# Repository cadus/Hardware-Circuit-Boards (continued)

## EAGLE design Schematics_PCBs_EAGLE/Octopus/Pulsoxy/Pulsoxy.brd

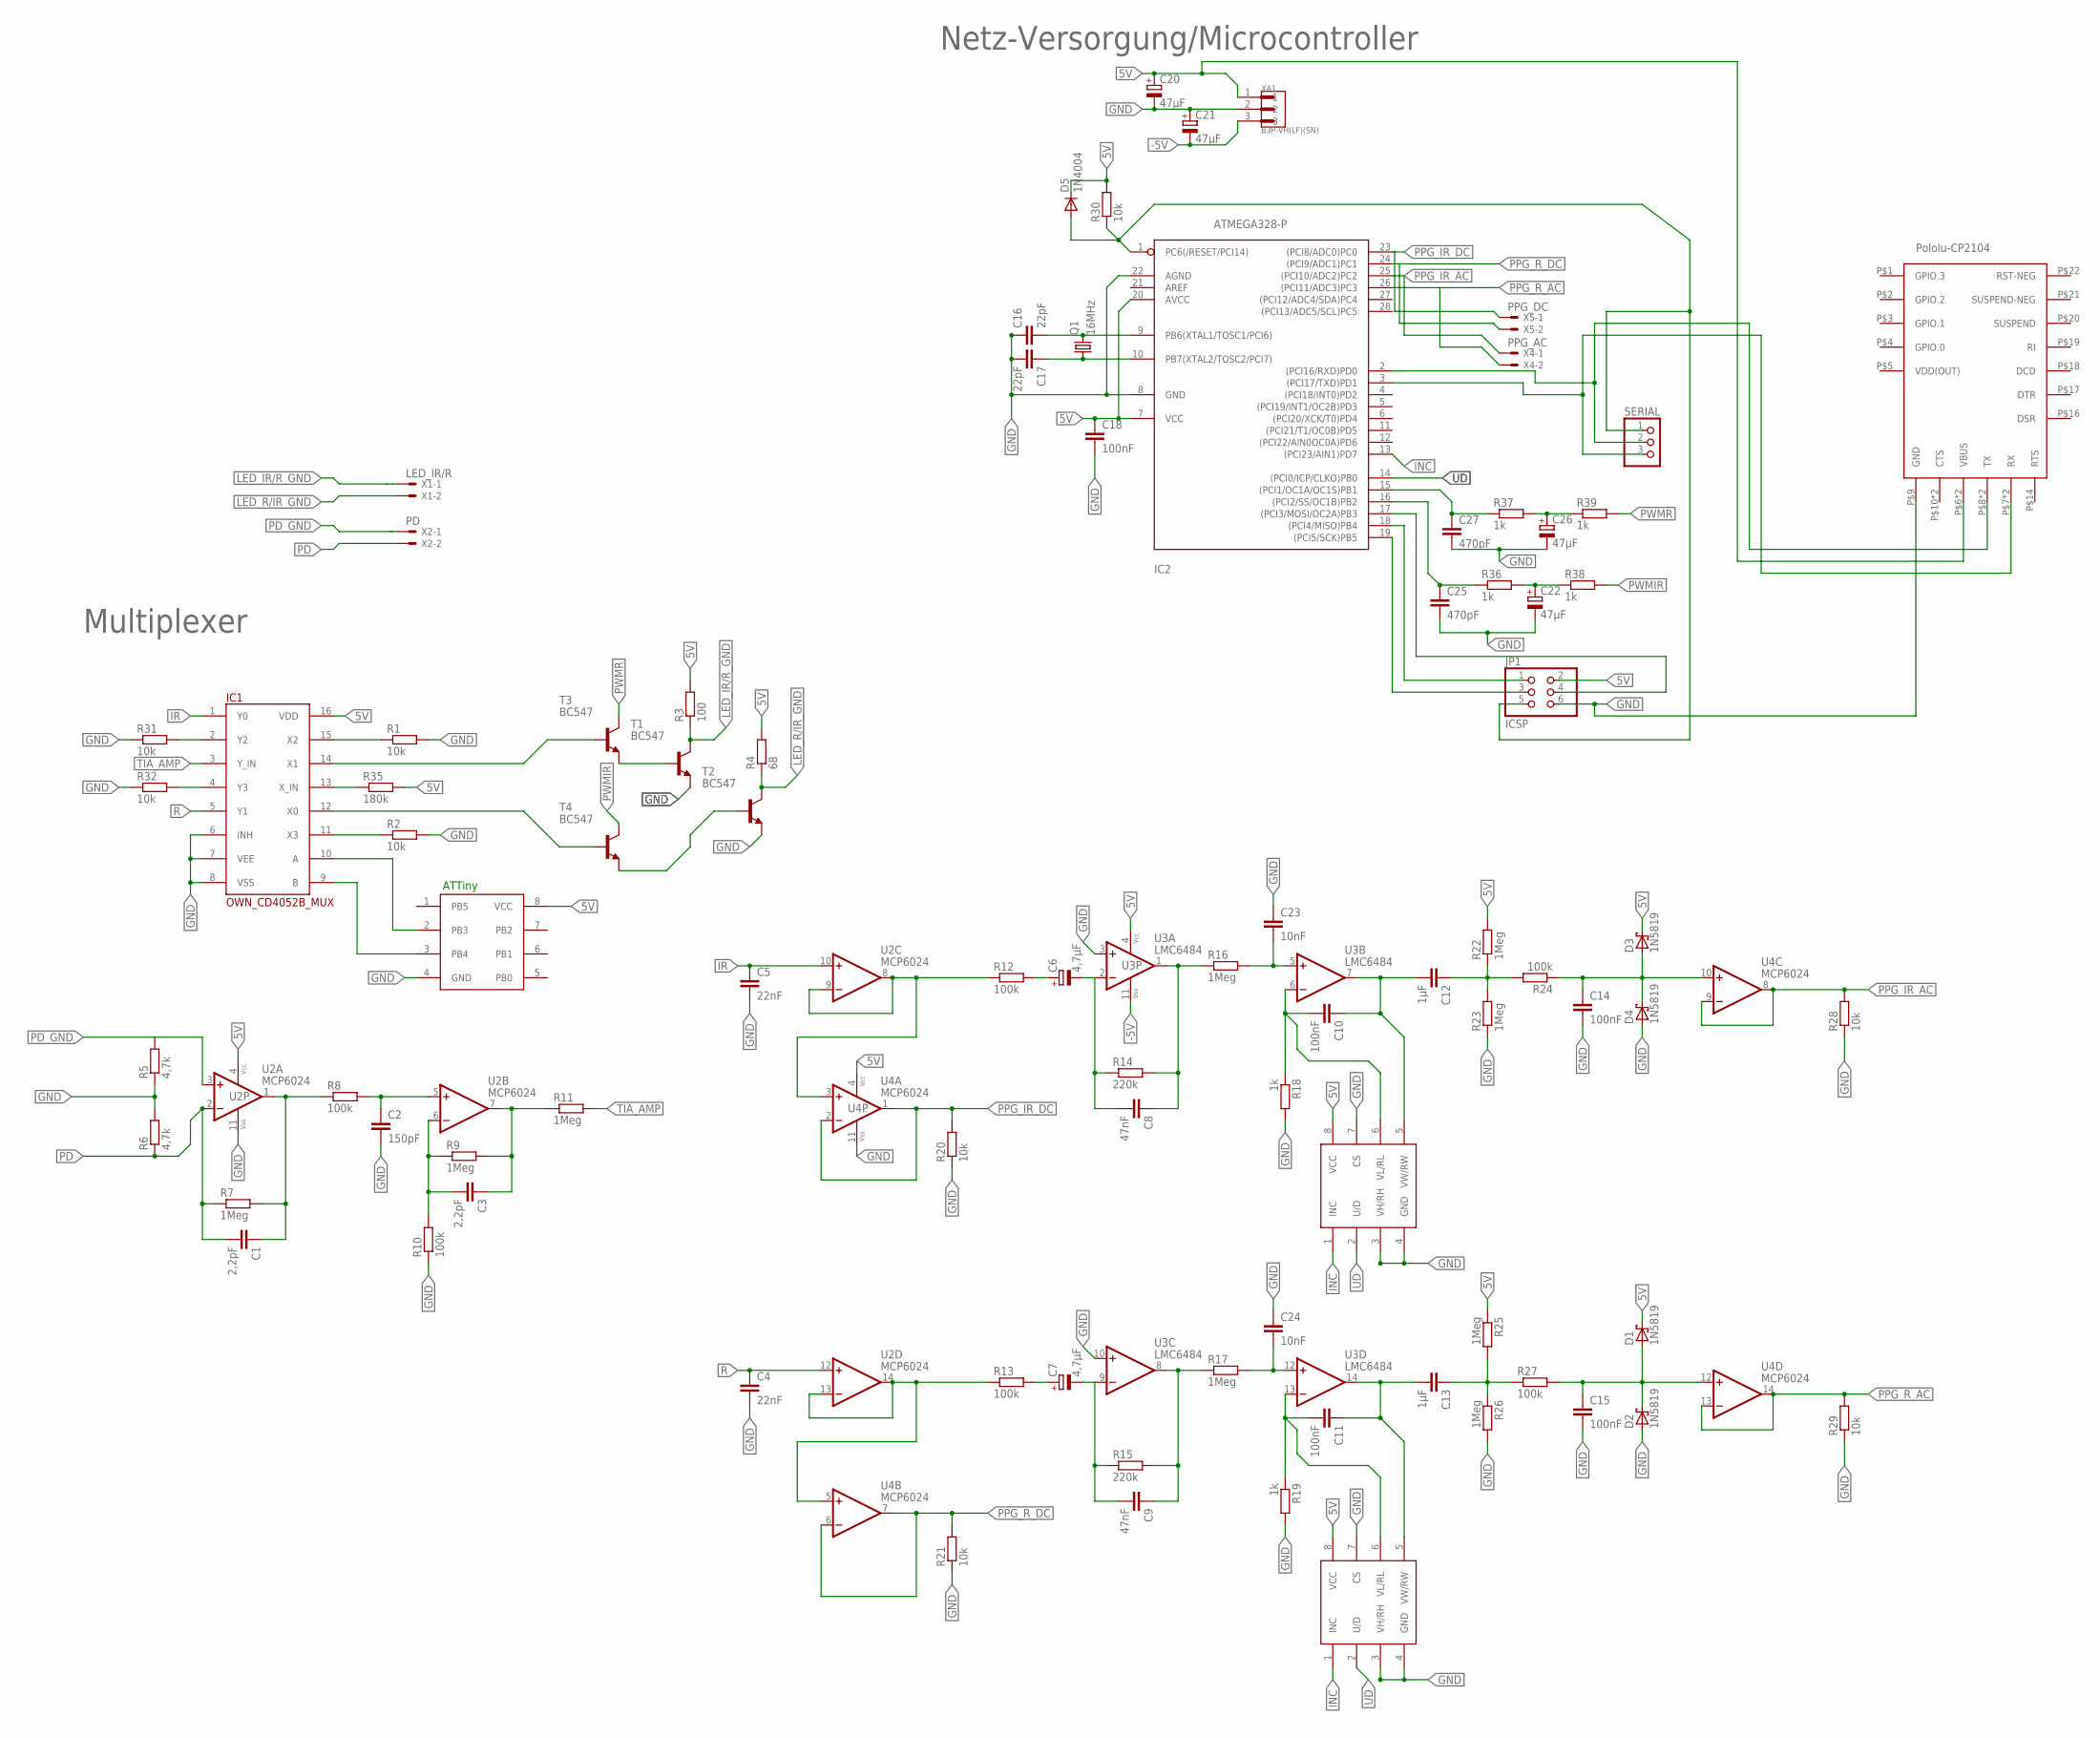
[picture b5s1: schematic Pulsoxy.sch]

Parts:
ATTINY: ATTINY85; DIL08
C1, C3: 2,2pF; C025-024X044
C2: 150pF; C025-024X044
C4, C5: 22nF; C025-024X044
C6, C7: 4,7µF; E2-5
C8, C9: 47nF; C025-024X044
C10, C11, C14, C15, C18: 100nF; C025-024X044
C12, C13: 1µF; C150-064X183
C16, C17: 22pF; C025-024X044
C20, C21, C22, C26: 47µF; E2,5-6E
C23, C24: 10nF; C025-024X044
C25, C27: 470pF; C025-024X044
D1, D2, D3, D4: 1N5819; F126Z12
D5: 1N4004; DO41-10
IC1: OWN_CD4052B_MUX; DIL16
IC2: ATMEGA328-P; DIL28-3
JP1: ICSP; 2X03
Q1: 16MHz; HC49U70
R1, R2, R20, R21, R28, R29, R30, R31, R32: 10k; 0204/7
R3: 100; 0204/7
R4: 68; 0204/7
R5, R6: 4,7k; 0204/7
R7, R9, R11, R16, R17, R22, R23, R25, R26: 1Meg; 0204/7
R8, R10, R12, R13, R24, R27: 100k; 0204/7
R14, R15: 220k; 0204/7
R18, R19, R36, R37, R38, R39: 1k; 0204/7
R35: 180k; 0204/7
SERIAL: PINHD-1X3; 1X03
T1, T2, T3, T4: BC547; TO92
U2, U4: MCP6024; DIL14
U3: LMC6484; DIL14
U$1, U$2: X9C104P; DIL08
U$3: POLOLU_CP2104; POLOLUCP2104
X1: LED_IR/R; JST-XH-02-PACKAGE-LONG-PAD
X2: PD; JST-XH-02-PACKAGE-LONG-PAD
X4: PPG_AC; JST-XH-02-PACKAGE-LONG-PAD
X5: PPG_DC; JST-XH-02-PACKAGE-LONG-PAD
XA1: B3P-VH(LF)(SN); JST_B3P-VH(LF)(SN)

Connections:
5V: ATTINY.8 (VCC), C18.1, C20.+, D1.C, D3.C, D5.C, IC1.16 (VDD), IC2.7 (VCC), IC2.20 (AVCC), JP1.2, R3.2, R4.2, R22.2, R25.1, R30.2, R35.2, U2.4 (VCC+), U3.4 (VCC+), U4.4 (VCC+), U$1.8 (VCC), U$2.8 (VCC), U$3.P$6 (VBUS), U$3.P$11 (VBUS), XA1.1
-5V: C21.-, U3.11 (VCC-), XA1.3
GND: ATTINY.4 (GND), C2.2, C4.2, C5.2, C14.2, C15.2, C16.1, C17.2, C18.2, C20.-, C21.+, C22.-, C23.1, C24.1, C25.2, C26.-, C27.2, D2.A, D4.A, IC1.6 (INH), IC1.7 (VEE), IC1.8 (VSS), IC2.8 (GND), IC2.22 (AGND), JP1.6, R1.2, R2.2, R5.1, R6.2, R10.1, R18.2, R19.2, R20.1, R21.1, R23.1, R26.2, R28.1, R29.1, R31.1, R32.1, T1.1 (E), T2.1 (E), U2.11 (VCC-), U3.3 (+IN), U3.10 (+IN), U4.11 (VCC-), U$1.3 (VH/RH), U$1.4 (GND), U$1.7 (CS), U$2.3 (VH/RH), U$2.4 (GND), U$2.7 (CS), U$3.P$9 (GND), XA1.2
INC: IC2.13 ((PCI23/AIN1)PD7), U$1.1 (INC), U$2.1 (INC)
IR: C5.1, IC1.1 (Y0), U2.10 (+IN)
LED_IR/R_GND: R3.1, T1.3 (C), X1.1
LED_R/IR_GND: R4.1, T2.3 (C), X1.2
unnamed: IC1.11 (X3), R2.1
unnamed: IC1.15 (X2), R1.1
unnamed: IC1.14 (X1), T3.2 (B)
unnamed: IC1.12 (X0), T4.2 (B)
unnamed: C1.1, R7.2, R8.1, U2.1 (OUT)
unnamed: C2.1, R8.2, U2.5 (+IN)
unnamed: C3.2, R9.1, R10.2, U2.6 (-IN)
unnamed: C3.1, R9.2, R11.1, U2.7 (OUT)
unnamed: R12.1, U2.8 (OUT), U2.9 (-IN), U4.3 (+IN)
unnamed: R13.1, U2.13 (-IN), U2.14 (OUT), U4.5 (+IN)
unnamed: ATTINY.2 (PB3), IC1.10 (A)
unnamed: ATTINY.3 (PB4), IC1.9 (B)
unnamed: C7.-, C9.2, R15.1, U3.9 (-IN)
unnamed: C8.1, R14.2, R16.1, U3.1 (OUT)
unnamed: C6.-, C8.2, R14.1, U3.2 (-IN)
unnamed: C9.1, R15.2, R17.1, U3.8 (OUT)
unnamed: C13.1, R25.2, R26.1, R27.1
unnamed: C14.1, D3.A, D4.C, R24.1, U4.10 (+IN)
unnamed: C10.2, R18.1, U3.6 (-IN), U$1.6 (VL/RL)
unnamed: C15.1, D1.A, D2.C, R27.2, U4.12 (+IN)
unnamed: C11.2, R19.1, U3.13 (-IN), U$2.6 (VL/RL)
unnamed: IC1.4 (Y3), R32.2
unnamed: C10.1, C12.2, U3.7 (OUT), U$1.5 (VW/RW)
unnamed: C12.1, R22.1, R23.2, R24.2
unnamed: C11.1, C13.2, U3.14 (OUT), U$2.5 (VW/RW)
unnamed: C16.2, IC2.9 (PB6(XTAL1/TOSC1/PCI6)), Q1.2
unnamed: C17.1, IC2.10 (PB7(XTAL2/TOSC2/PCI7)), Q1.1
unnamed: IC2.2 ((PCI16/RXD)PD0), SERIAL.2, U$3.P$8 (TX), U$3.P$12 (TX)
unnamed: D5.A, IC2.1 (PC6(/RESET/PCI14)), JP1.5, R30.1, SERIAL.1
unnamed: IC2.18 ((PCI4/MISO)PB4), JP1.1
unnamed: IC2.19 ((PCI5/SCK)PB5), JP1.3
unnamed: IC2.17 ((PCI3/MOSI/OC2A)PB3), JP1.4
unnamed: IC1.2 (Y2), R31.2
unnamed: IC2.3 ((PCI17/TXD)PD1), SERIAL.3, U$3.P$7 (RX), U$3.P$13 (RX)
unnamed: C24.2, R17.2, U3.12 (+IN)
unnamed: IC1.13 (X_IN), R35.1
unnamed: C25.1, IC2.16 ((PCI2/SS/OC1B)PB2), R36.1
unnamed: C23.2, R16.2, U3.5 (+IN)
unnamed: C7.+, R13.2
unnamed: C6.+, R12.2
unnamed: T1.2 (B), T3.1 (E)
unnamed: T2.2 (B), T4.1 (E)
unnamed: C22.+, R36.2, R38.1
unnamed: C27.1, IC2.15 ((PCI1/OC1A/OC1S)PB1), R37.1
unnamed: C26.+, R37.2, R39.1
PD: C1.2, R6.1, R7.1, U2.2 (-IN), X2.2
PD_GND: R5.2, U2.3 (+IN), X2.1
PPG_IR_AC: IC2.25 ((PCI10/ADC2)PC2), R28.2, U4.8 (OUT), U4.9 (-IN), X4.1
PPG_IR_DC: IC2.23 ((PCI8/ADC0)PC0), R20.2, U4.1 (OUT), U4.2 (-IN), X5.1
PPG_R_AC: IC2.26 ((PCI11/ADC3)PC3), R29.2, U4.13 (-IN), U4.14 (OUT), X4.2
PPG_R_DC: IC2.24 ((PCI9/ADC1)PC1), R21.2, U4.6 (-IN), U4.7 (OUT), X5.2
PWMIR: R38.2, T4.3 (C)
PWMR: R39.2, T3.3 (C)
R: C4.1, IC1.5 (Y1), U2.12 (+IN)
TIA_AMP: IC1.3 (Y_IN), R11.2
UD: IC2.14 ((PCI0/ICP/CLKO)PB0), U$1.2 (U/D), U$2.2 (U/D)
VDD(OUT): U$3.P$5 (VDD(OUT))

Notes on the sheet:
ATTiny
Netz-Versorgung/Microcontroller
Multiplexer

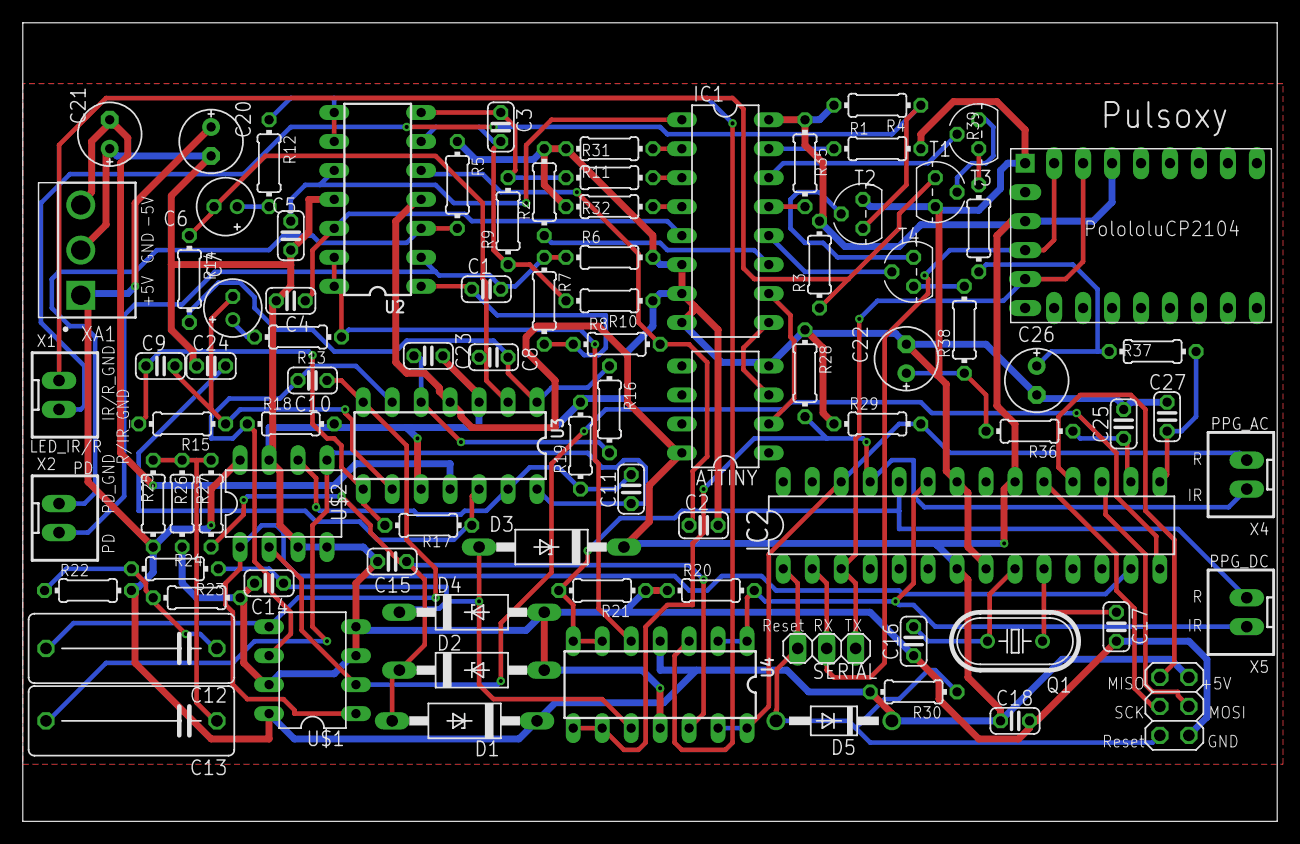
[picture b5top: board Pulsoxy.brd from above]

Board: 2 copper layers, 110.0 x 70.0 mm, 89 parts (0 on the bottom side), 63 nets.

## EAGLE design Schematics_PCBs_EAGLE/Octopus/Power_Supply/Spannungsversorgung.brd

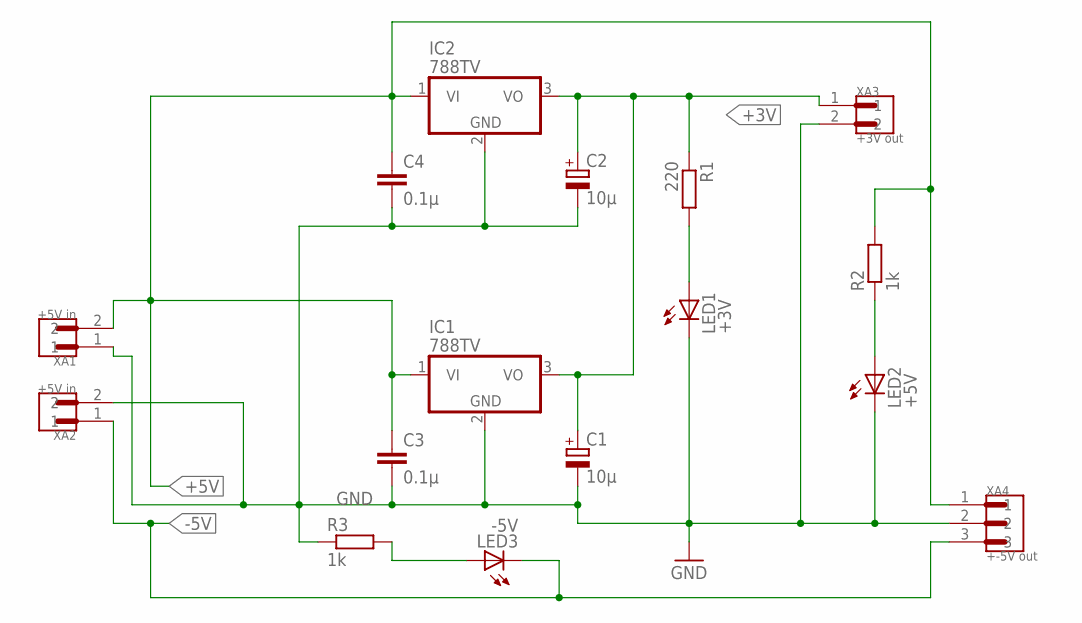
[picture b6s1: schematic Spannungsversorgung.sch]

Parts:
C1, C2: 10µ; E2,5-6
C3, C4: 0.1µ; C2.5-3
IC1, IC2: 788TV; TO220V
LED1: +3V; LED3MM
LED2: +5V; LED3MM
LED3: -5V; LED3MM
R1: 220; 0207/7
R2, R3: 1k; 0207/7
XA1, XA2: +5V in; JST_B2P-VH(LF)(SN)
XA3: +3V out; JST_B2P-VH(LF)(SN)
XA4: +-5V out; JST_B3P-VH(LF)(SN)

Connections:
+3V: C1.+, C2.+, IC1.3 (VO), IC2.3 (VO), R1.1, XA3.1
+5V: C3.1, C4.1, IC1.1 (VI), IC2.1 (VI), R2.2, XA1.2, XA4.1
-5V: LED3.K (C), XA2.1, XA4.3
GND: C1.-, C2.-, C3.2, C4.2, IC1.2 (GND), IC2.2 (GND), LED1.K (C), LED2.K (C), R3.1, XA1.1, XA2.2, XA3.2, XA4.2
unnamed: LED3.A, R3.2
unnamed: LED1.A, R1.2
unnamed: LED2.A, R2.1

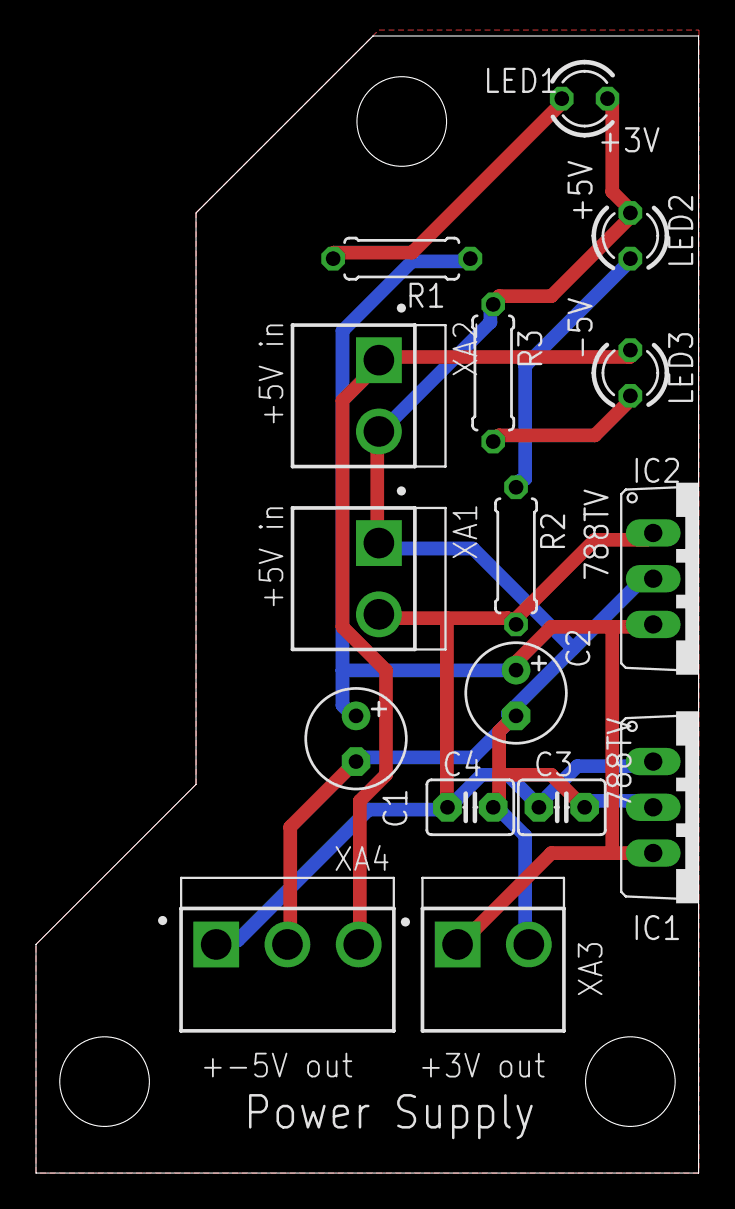
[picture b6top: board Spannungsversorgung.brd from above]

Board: 2 copper layers, 36.8 x 63.2 mm, 16 parts (0 on the bottom side), 7 nets.

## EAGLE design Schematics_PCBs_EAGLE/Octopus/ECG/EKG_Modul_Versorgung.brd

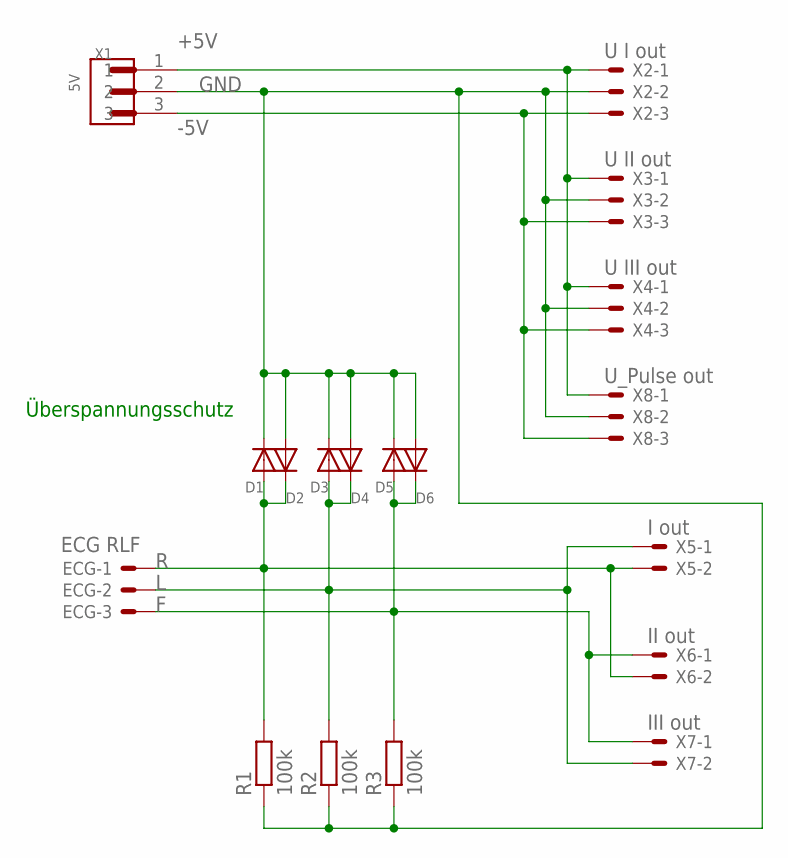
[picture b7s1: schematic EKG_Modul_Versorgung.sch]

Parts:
D1, D2, D3, D4, D5, D6: DIODEDO-1N4148; DO-1N4148
ECG: ECG RLF; JST-XH-03-PACKAGE-LONG-PAD
R1, R2, R3: 100k; 0207/7
X1: 5V; JST_B3P-VH(LF)(SN)
X2: U I out; JST-XH-03-PACKAGE-LONG-PAD
X3: U II out; JST-XH-03-PACKAGE-LONG-PAD
X4: U III out; JST-XH-03-PACKAGE-LONG-PAD
X5: I out; JST-XH-02-PACKAGE-LONG-PAD
X6: II out; JST-XH-02-PACKAGE-LONG-PAD
X7: III out; JST-XH-02-PACKAGE-LONG-PAD
X8: U_Pulse out; JST-XH-03-PACKAGE-LONG-PAD

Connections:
+5V: X1.1, X2.1, X3.1, X4.1, X8.1
-5V: X1.3, X2.3, X3.3, X4.3, X8.3
F: D5.A, D6.C, ECG.3, R3.2, X6.1, X7.1
GND: D1.C, D2.A, D3.C, D4.A, D5.C, D6.A, R1.1, R2.1, R3.1, X1.2, X2.2, X3.2, X4.2, X8.2
L: D3.A, D4.C, ECG.2, R2.2, X5.1, X7.2
R: D1.A, D2.C, ECG.1, R1.2, X5.2, X6.2

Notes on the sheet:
Überspannungsschutz

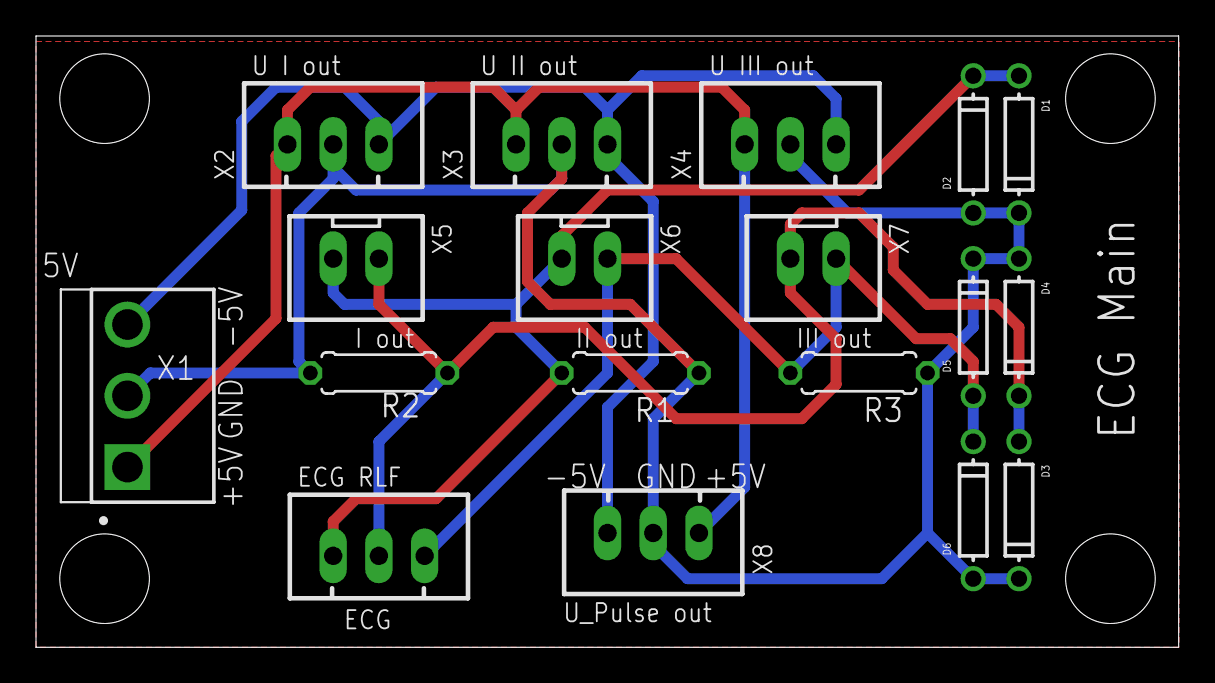
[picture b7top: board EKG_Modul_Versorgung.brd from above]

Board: 2 copper layers, 63.5 x 34.0 mm, 18 parts (0 on the bottom side), 6 nets.

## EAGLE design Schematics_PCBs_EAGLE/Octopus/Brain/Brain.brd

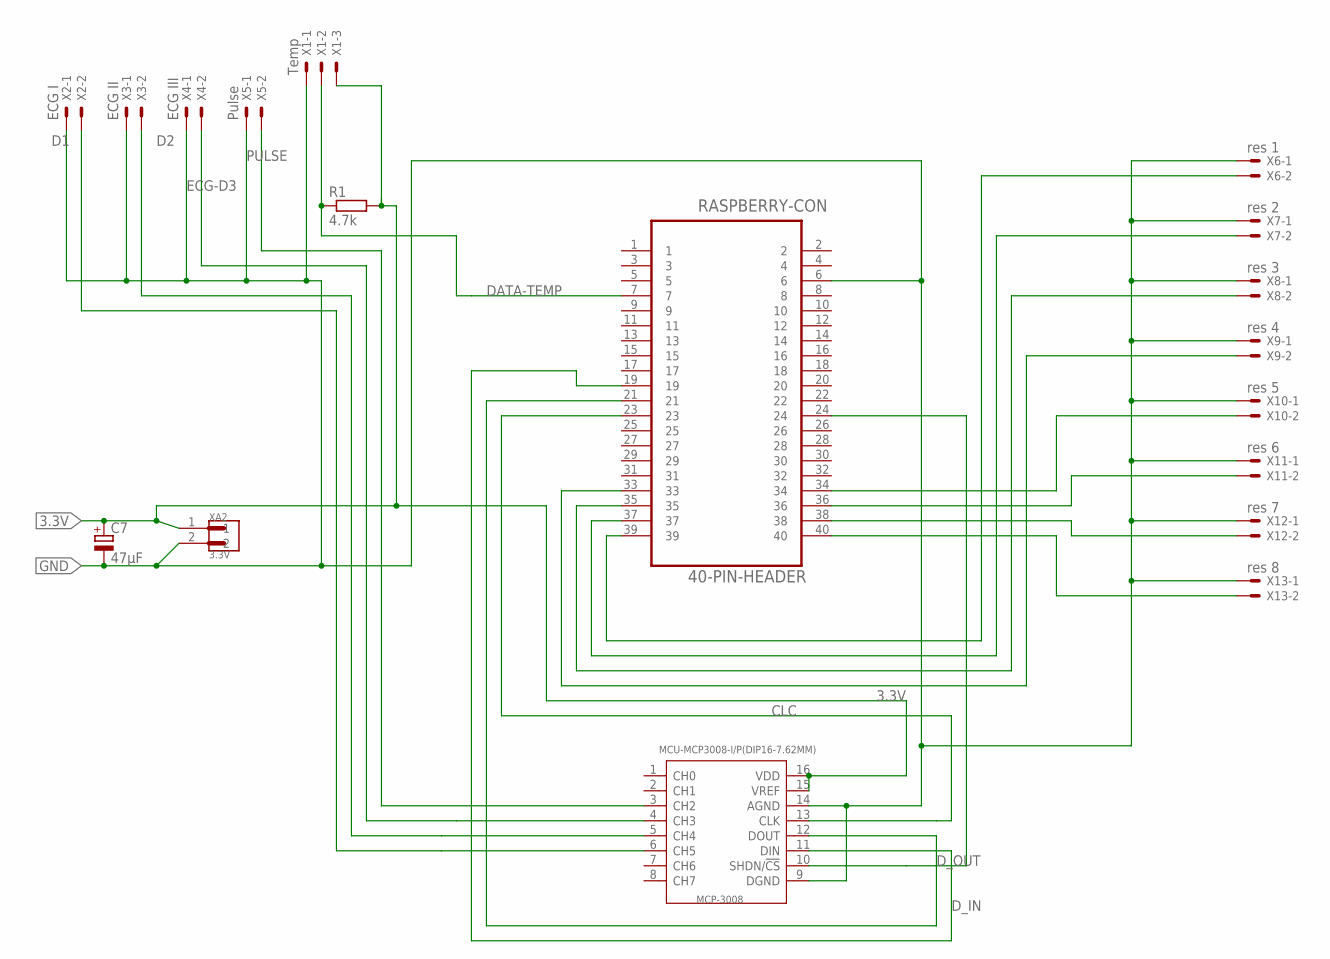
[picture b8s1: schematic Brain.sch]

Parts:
C7: 47µF; E2,5-6E
MCP-3008: MCU-MCP3008-I/P(DIP16-7.62MM); DIP16-2.54-19.2X7.62MM
R1: 4.7k; 0207/7
RASPBERRY-CON: 40-PIN-HEADER; SAMTEC_TSW-120-09-F-Q
X1: Temp; JST-XH-03-PACKAGE-LONG-PAD
X2: ECG I; JST-XH-02-PACKAGE-LONG-PAD
X3: ECG II; JST-XH-02-PACKAGE-LONG-PAD
X4: ECG III; JST-XH-02-PACKAGE-LONG-PAD
X5: Pulse; JST-XH-02-PACKAGE-LONG-PAD
X6: res 1; JST-XH-02-PACKAGE-LONG-PAD
X7: res 2; JST-XH-02-PACKAGE-LONG-PAD
X8: res 3; JST-XH-02-PACKAGE-LONG-PAD
X9: res 4; JST-XH-02-PACKAGE-LONG-PAD
X10: res 5; JST-XH-02-PACKAGE-LONG-PAD
X11: res 6; JST-XH-02-PACKAGE-LONG-PAD
X12: res 7; JST-XH-02-PACKAGE-LONG-PAD
X13: res 8; JST-XH-02-PACKAGE-LONG-PAD
XA2: 3.3V; JST_B2P-VH(LF)(SN)

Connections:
3.3V: C7.+, MCP-3008.15 (VREF), MCP-3008.16 (VDD), R1.2, X1.3, XA2.1
CLC: MCP-3008.13 (CLK), RASPBERRY-CON.23
D1: MCP-3008.6 (CH5), X2.2
D2: MCP-3008.5 (CH4), X3.2
DATA-TEMP: R1.1, RASPBERRY-CON.7, X1.2
D_IN: MCP-3008.11 (DIN), RASPBERRY-CON.19
D_OUT: MCP-3008.12 (DOUT), RASPBERRY-CON.21
ECG-D3: MCP-3008.4 (CH3), X4.2
GND: C7.-, MCP-3008.9 (DGND), MCP-3008.14 (AGND), RASPBERRY-CON.6, X1.1, X2.1, X3.1, X4.1, X5.1, X6.1, X7.1, X8.1, X9.1, X10.1, X11.1, X12.1, X13.1, XA2.2
unnamed: RASPBERRY-CON.40, X13.2
unnamed: RASPBERRY-CON.38, X12.2
unnamed: MCP-3008.10 (SHDN/!CS), RASPBERRY-CON.24
unnamed: RASPBERRY-CON.36, X11.2
unnamed: RASPBERRY-CON.34, X10.2
unnamed: RASPBERRY-CON.39, X6.2
unnamed: RASPBERRY-CON.37, X7.2
unnamed: RASPBERRY-CON.35, X8.2
unnamed: RASPBERRY-CON.33, X9.2
PULSE: MCP-3008.3 (CH2), X5.2

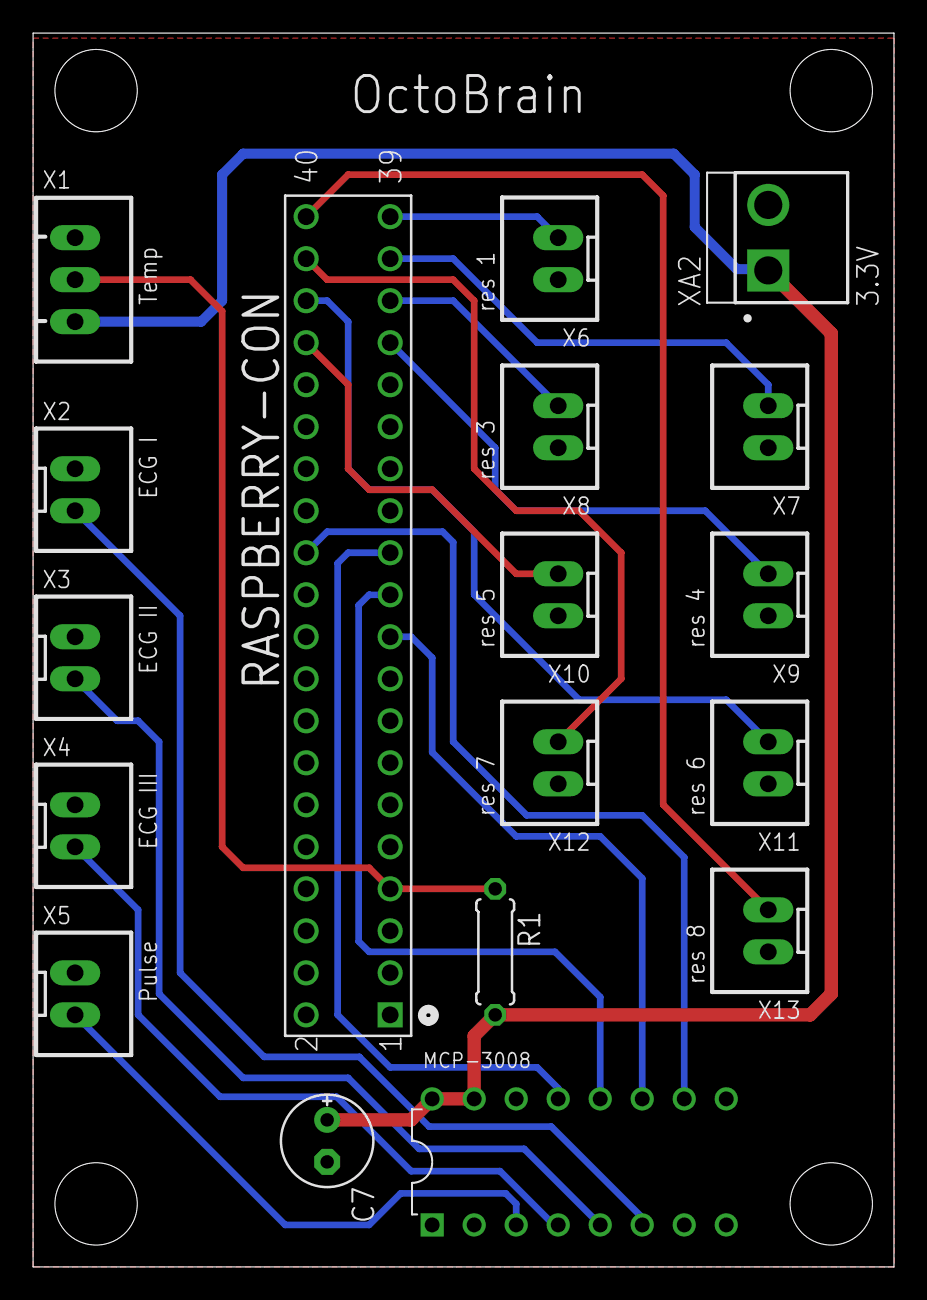
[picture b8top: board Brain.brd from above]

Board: 2 copper layers, 52.0 x 74.6 mm, 18 parts (0 on the bottom side), 19 nets.

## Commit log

2019-03-29 Electronic schematics and PCB Layouts
2019-03-29 Device files not included in standard EAGLE
2019-03-29 PCB gerber files
2019-03-29 Part lists for each PCB
2019-04-12 Source codes for microcontrollers
2019-06-25 Wiring schematics for PCB modules
2019-07-31 Wiring schematics for all PCB boards and power supply
2019-07-31 Add files via upload
    Description of electronic components and assembly instructions
2019-07-31 Create folder
    Schematics for circuit boards and PCB layouts as PNG and PDF files
2019-07-31 PCB layout of OctoBrain board
2020-03-14 arduino-pulsoxy: Import C sources from PULSOXYv0.0.1
    Copy .c and .h files from Driver/ Include/ Util/ and
    main.c from the original project. Put everything in
    one directory for the Arduino IDE to find everything.
2020-03-14 arduino-pulsoxy: Remove unused files
    CFile1.c and init_ADC.c do not contribute to the project.
    Remove these files. Also remove init_ADC.h header file.
    All ADC related functions are already declared and implemented
    in the ADC.c/.h files.
    Remove init_ADC.h header
2020-03-14 arduino-pulsoxy: Rename main.c to Arduino project file
    The .ino should have the same name as the containing
    folder for the Arduino IDE to recognize it.
2020-03-14 arduino-pulsoxy: Fix F_CPU redefined warnings
    F_CPU is usually already defined by the project makefile.
2020-03-14 arduino-pulsoxy: Include headers as extern "C"
    Prevent C++ name mangling when reading these functions.
2020-03-14 arduino-pulsoxy: Fix typo
2020-03-14 arduino-pulsoxy: Fix type mismatch in redeclaration
    These are ADC values that are used as signed int16 in the code.
2020-03-14 arduino-pulsoxy: Fix missing newline in all files
2020-03-14 arduino-pulsoxy: Add README file
2020-03-14 arduino-pulsoxy: Use setup() and loop() functions
    Split the main() function into setup() and loop() for classical
    Arduino feeling. Arduino will provide a main() that calls those.
2020-03-14 arduino-pulsoxy: Fix trailing whitespace in all files
